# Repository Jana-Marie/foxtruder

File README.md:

# permanently moved to [codeberg/janam/foxtruder](https://codeberg.org/janam/foxtruder)

# foxtruder

**~~froggy~~**, **~~fog-o-nozzle~~**, **~~multimist~~**, **foxtruder [working title]** is a tiny fog machine powered by USB-PD, with Wifi and Bluetooth, based around a 3D-printer heat-cartridge and nozzle. As much as I wish to call this the worlds smallest **intentional** fog machine, sadly disposable vapes exist. Otherwise this one would be atop of the smaller fog-machines. To make it this small however, it requires an external pump, or rather a pressurized fog-fluid line, which can be connected to the 4mm pneumatic connector at the bottom. The idea here is to just have one fog-juice reservoir and pump for many fog machines. A valve on the board is used to switch the fog.

 - **Size:** 70x70x35mm
 - **Power-In:** 12-24V DC, USB-PD
 - **Communication:** RS485, DMX, WIFI, BLE, USB (Python Shell)
 - **Indication:** 4 Status LEDs, 5 Effect LEDs
 - **IO:** RS485, External IO, 2 Buttons, 4mm pneumatic push connector (fluid in), Fan Connector, I2C

Now, you might ask **why**?? To be clear, this is a stupid idea, an intrusive thought turned reality if you will, I'm not even sure if I can recommend you to replicate this. However, the tiny size combined with the low cost per machine of ~20-40€ makes this perfect for larger art-installations requiring fog. Or even better use the fog as the medium of visual art. I.e. in an array, linear arrangement, circular fashion or just many small distributed points of fog generation.

<table>
  <tbody>
    <tr>
      <td>
        
      </td>
      <td>
        
      </td>
    </tr>
  </tbody>
</table>

I guess this exists now, enjoy?.

<table>
  <tbody>
    <tr>
      <td width="68%">
        
      </td>
      <td>
        
      </td>
    </tr>
  </tbody>
</table>

### State of this project and learnings

**It is not recommended to replicate this project in its current form, it is more of an experiment than a proper fog machine.** Issues to be solved include but are not limited to:

 - Spitting, the fog machine tends to not convert all fog-juice into fog
 - BOM cost, it should be optimized
 - Mechanical complexity, the valve-hotend interface requires some odd machining
 - Assembly complexity is too high
 - Open health questions, it seems that fog-juice may be unhealthy when heated above 190°C, however for a proper, spit-free operation temperatures well above 250-300°C might be desired (as with commercial fog machines)

### FAQ

##### Can this be run off a MacBooks USB-PD port?

Yes, that was the main mean of development.

### Initial block diagram

This needs updating, but this was the initial idea. The fog-juice tank is an external component now and the additional airflow controller to disturb the fog has not been implemented yet. Otherwise this is fairly true to foxtruder. The fog-juice tank is a real thing and has an input for pressurized air and an outlet for the liquid.

<table>
  <tbody>
    <tr>
      <td>
        
      </td>
    </tr>
  </tbody>
</table>

### On the name

Finding a name for this project was surprisingly complicated, we just included all names we came up with. The initial idea was to "paint it green and call it froggy", like a foggy small frog sitting in the morning mist of a luscious lawn. Then we went towards focussing on the nozzle, the snoot and eventually we arrived at foxtruder, just... don't boop it, it *will* bite.

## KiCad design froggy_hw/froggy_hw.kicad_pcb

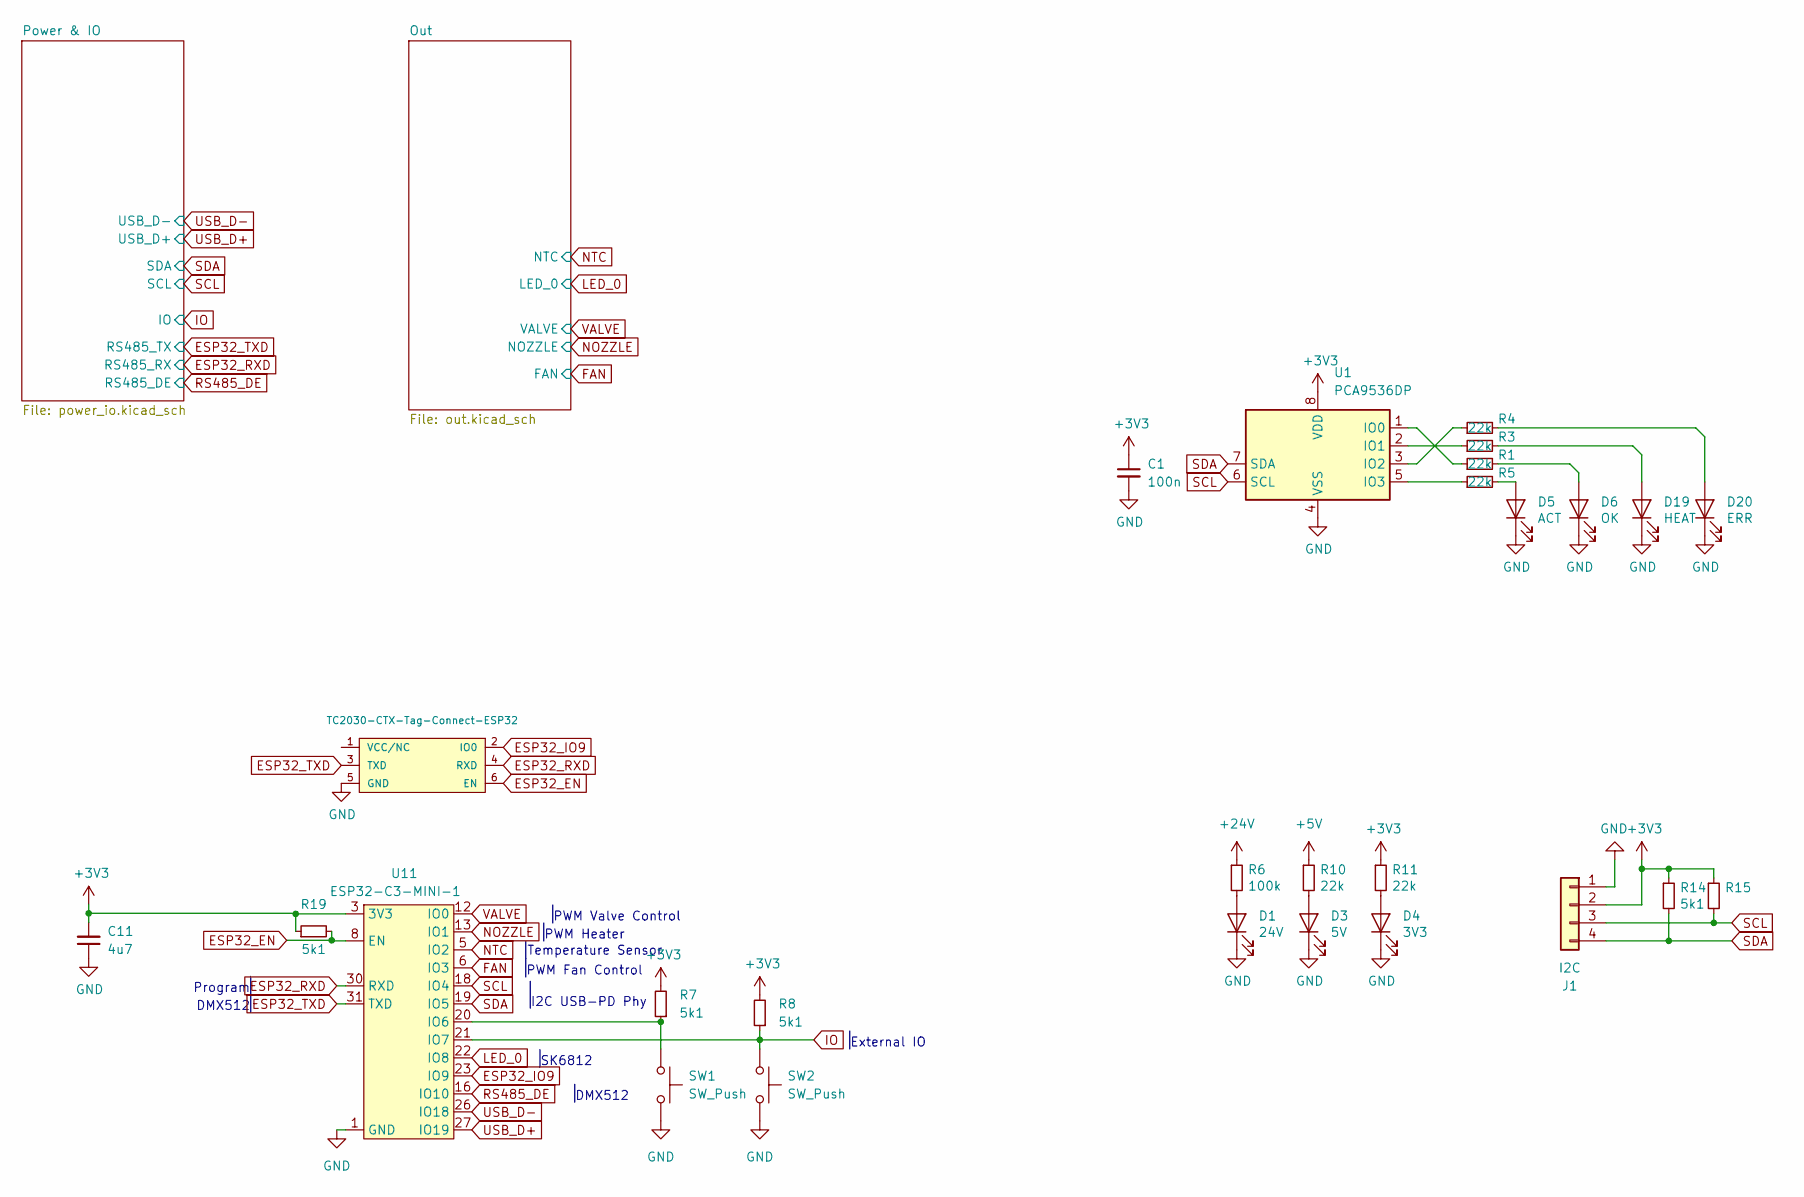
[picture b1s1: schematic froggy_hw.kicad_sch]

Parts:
C1: 100n; C_0402
C11: 4u7; C_0805
D1: 24V; LED_0603_1608Metric
D3: 5V; LED_0603_1608Metric
D4: 3V3; LED_0603_1608Metric
D5: ACT; LED_0603_1608Metric
D6: OK; LED_0603_1608Metric
D19: HEAT; LED_0603_1608Metric
D20: ERR; LED_0603_1608Metric
J1: I2C; PinHeader_1x04_P2.54mm_Vertical_SMD_Pin1Left
P2: TC2030-CTX-Tag-Connect-ESP32; TC2030
R1, R3, R4, R5, R10, R11: 22k; R_0402
R6: 100k; R_0402
R7, R8, R14, R15, R19: 5k1; R_0402
SW1, SW2: SW_Push; SW_SPST_EVQP7C
U1: PCA9536DP; TSSOP-8_3x3mm_P0.65mm
U11: ESP32-C3-MINI-1

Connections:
+3V3: C1.1, C11.2, J1.2, R7.2, R8.2, R11.1, R14.1, R15.1, R19.1, U1.8 (VDD), U11.3 (3V3); also elsewhere on the board
+5V: R10.1; also elsewhere on the board
+24V: R6.1; also elsewhere on the board
ESP32_EN: P2.6 (EN), R19.2, U11.8 (EN)
ESP32_IO9: P2.2 (IO0), U11.23 (IO9)
ESP32_RXD: P2.4 (RXD), U11.30 (RXD); also elsewhere on the board
ESP32_TXD: P2.3 (TXD), U11.31 (TXD); also elsewhere on the board
FAN: U11.6 (IO3)
GND: C1.2, C11.1, D1.1 (K), D3.1 (K), D4.1 (K), D5.1 (K), D6.1 (K), D19.1 (K), D20.1 (K), J1.1, P2.5 (GND), SW1.2, SW2.2, U1.4 (VSS), U11.1 (GND), U11.2 (GND), U11.11 (GND), U11.14 (GND), U11.36 (GND), U11.37 (GND), U11.38 (GND), U11.39 (GND), U11.40 (GND), U11.41 (GND), U11.42 (GND), U11.43 (GND), U11.44 (GND), U11.45 (GND), U11.46 (GND), U11.47 (GND), U11.48 (GND), U11.49 (GND), U11.50 (GND), U11.51 (GND), U11.52 (GND), U11.53 (GND); also elsewhere on the board
IO: R8.1, SW2.1, U11.21 (IO7); also elsewhere on the board
LED_0: U11.22 (IO8); also elsewhere on the board
NOZZLE: U11.13 (IO1); also elsewhere on the board
NTC: U11.5 (IO2); also elsewhere on the board
unnamed: D1.2 (A), R6.2
unnamed: D3.2 (A), R10.2
unnamed: D4.2 (A), R11.2
unnamed: D5.2 (A), R5.2
unnamed: D6.2 (A), R1.2
unnamed: D19.2 (A), R3.2
unnamed: D20.2 (A), R4.2
unnamed: R1.1, U1.1 (IO0)
unnamed: R3.1, U1.2 (IO1)
unnamed: R4.1, U1.3 (IO2)
unnamed: R5.1, U1.5 (IO3)
unnamed: R7.1, SW1.1, U11.20 (IO6)
RS485_DE: U11.16 (IO10); also elsewhere on the board
SCL: J1.3, R15.2, U1.6 (SCL), U11.18 (IO4); also elsewhere on the board
SDA: J1.4, R14.2, U1.7 (SDA), U11.19 (IO5); also elsewhere on the board
USB_D+: U11.27 (IO19); also elsewhere on the board
USB_D-: U11.26 (IO18); also elsewhere on the board
VALVE: U11.12 (IO0); also elsewhere on the board

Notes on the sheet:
External IO
SK6812
PWM Fan Control
PWM Valve Control
DMX512
PWM Heater
Temperature Sensor
Program
I2C USB-PD Phy

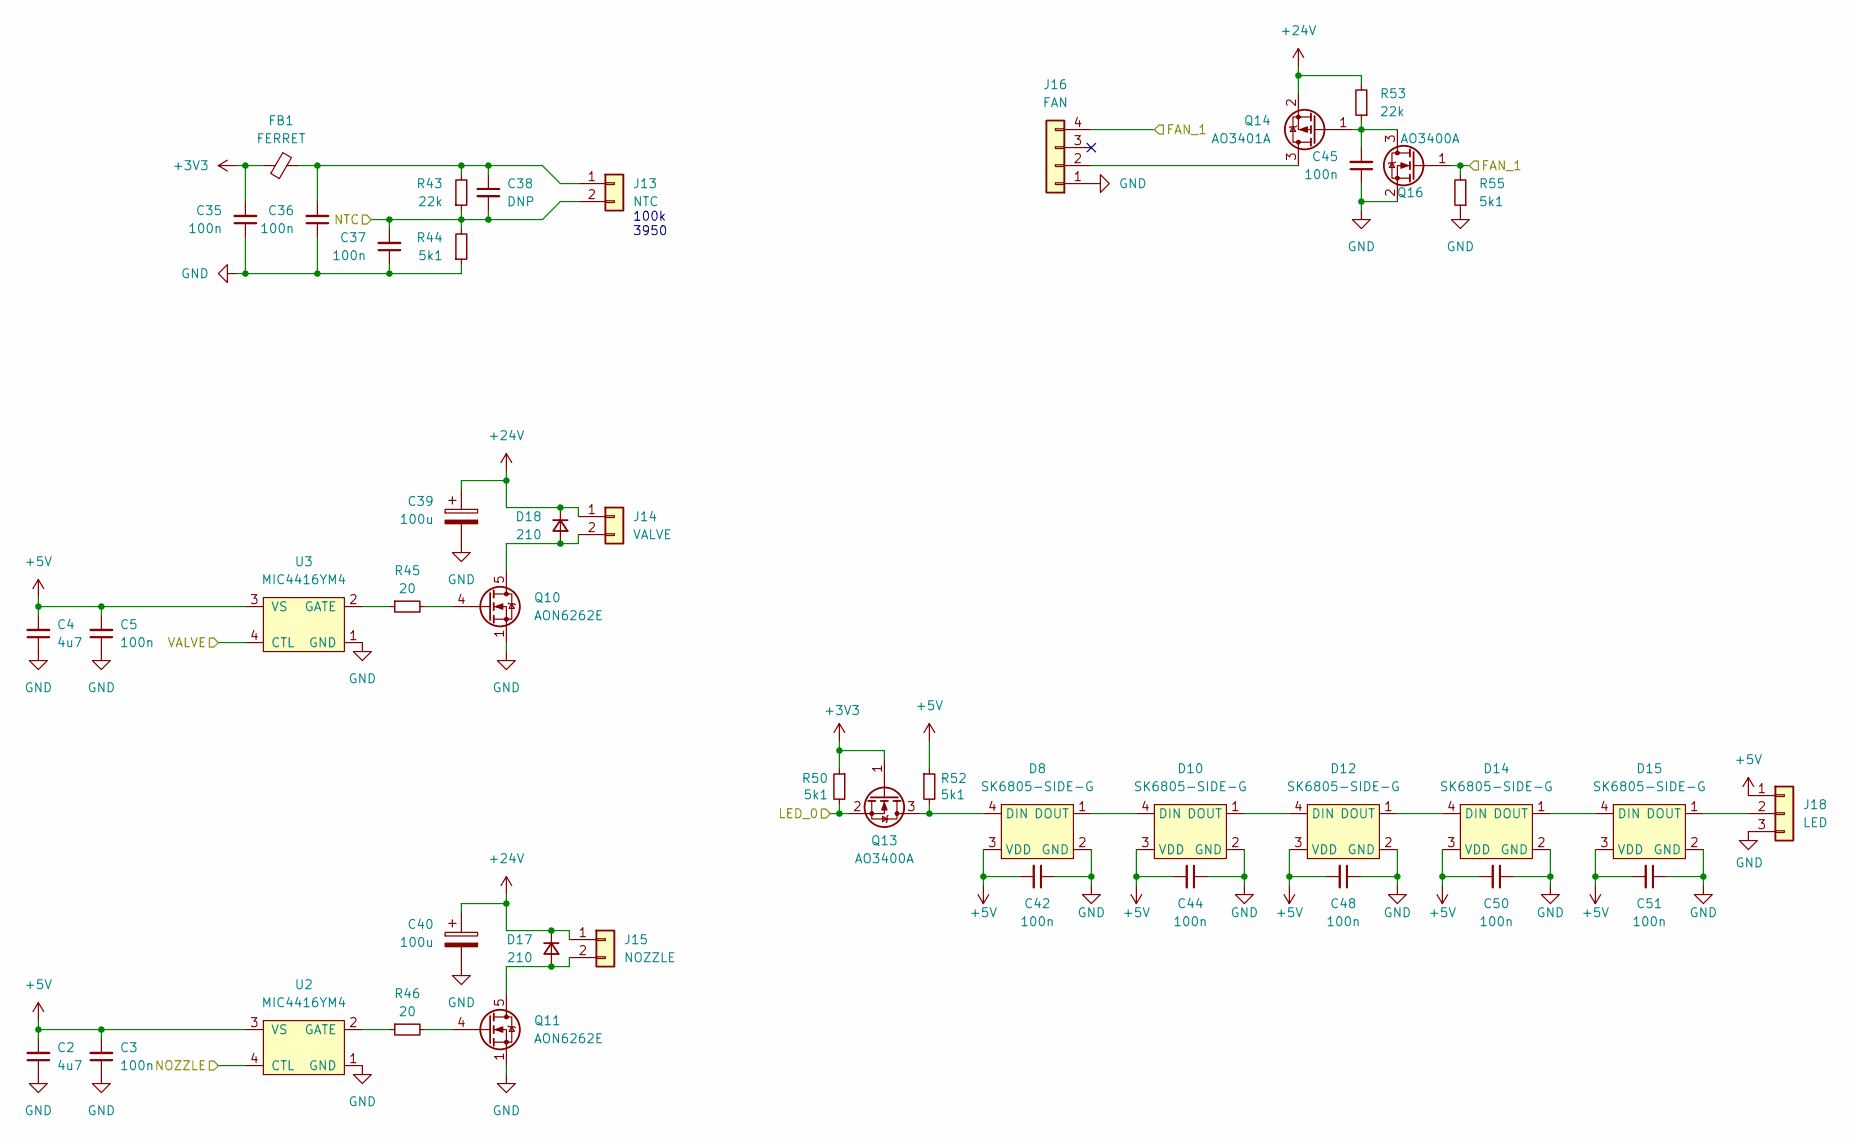
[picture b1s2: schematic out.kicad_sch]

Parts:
C2, C4: 4u7; C_0805
C3, C5, C35, C36, C37, C42, C44, C45, C48, C50, C51: 100n; C_0402
C38: DNP; C_0402
C39, C40: 100u; CP_Radial_D6.3mm_P2.50mm
D8, D10, D12, D14, D15: SK6805-SIDE-G
D17, D18: 210; D_SOD-123F
FB1: FERRET; R_0805
J13: NTC; PinHeader_1x02_P2.54mm_Vertical
J14: VALVE; PhoenixContact_MCV_1,5_2-G-3.5_1x02_P3.50mm_Vertical
J15: NOZZLE; PhoenixContact_MCV_1,5_2-G-3.5_1x02_P3.50mm_Vertical
J16: FAN; Molex_KK-254_AE-6410-04A_1x04_P2.54mm_Vertical
J18: LED; PinHeader_1x03_P2.54mm_Horizontal
Q10, Q11: AON6262E; TDSON-8-1
Q13, Q16: AO3400A; SOT-23
Q14: AO3401A; SOT-23
R43, R53: 22k; R_0402
R44, R50, R52, R55: 5k1; R_0402
R45, R46: 20; R_0805
U2, U3: MIC4416YM4; SOT-143

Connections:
+3V3: C35.2, FB1.1, Q13.1 (G), R50.1; also elsewhere on the board
+5V: C2.2, C3.2, C4.2, C5.2, C42.2, C44.2, C48.2, C50.2, C51.2, D8.3 (VDD), D10.3 (VDD), D12.3 (VDD), D14.3 (VDD), D15.3 (VDD), J18.1, R52.1, U2.3 (VS), U3.3 (VS); also elsewhere on the board
+24V: C39.1, C40.1, D17.1 (K), D18.1 (K), J14.1, J15.1, Q14.2 (S), R53.2; also elsewhere on the board
/Out/FAN_1: J16.4, Q16.1 (G), R55.2
GND: C2.1, C3.1, C4.1, C5.1, C35.1, C36.1, C37.1, C39.2, C40.2, C42.1, C44.1, C45.1, C48.1, C50.1, C51.1, D8.2 (GND), D10.2 (GND), D12.2 (GND), D14.2 (GND), D15.2 (GND), J16.1, J18.3, Q10.1 (S), Q10.2 (S), Q10.3 (S), Q11.1 (S), Q11.2 (S), Q11.3 (S), Q16.2 (S), R44.1, R55.1, U2.1 (GND), U3.1 (GND); also elsewhere on the board
LED_0: Q13.2 (S), R50.2; also elsewhere on the board
NOZZLE: U2.4 (CTL); also elsewhere on the board
NTC: C37.2, C38.2, J13.2, R43.1, R44.2; also elsewhere on the board
unnamed: D8.4 (DIN), Q13.3 (D), R52.2
unnamed: D8.1 (DOUT), D10.4 (DIN)
unnamed: D10.1 (DOUT), D12.4 (DIN)
unnamed: D12.1 (DOUT), D14.4 (DIN)
unnamed: D14.1 (DOUT), D15.4 (DIN)
unnamed: D15.1 (DOUT), J18.2
unnamed: D17.2 (A), J15.2, Q11.5 (D)
unnamed: D18.2 (A), J14.2, Q10.5 (D)
unnamed: C36.2, C38.1, FB1.2, J13.1, R43.2
unnamed: J16.2, Q14.3 (D)
unnamed: Q10.4 (G), R45.2
unnamed: Q11.4 (G), R46.2
unnamed: C45.2, Q14.1 (G), Q16.3 (D), R53.1
unnamed: R46.1, U2.2 (GATE)
unnamed: R45.1, U3.2 (GATE)
VALVE: U3.4 (CTL); also elsewhere on the board

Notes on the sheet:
100k 3950

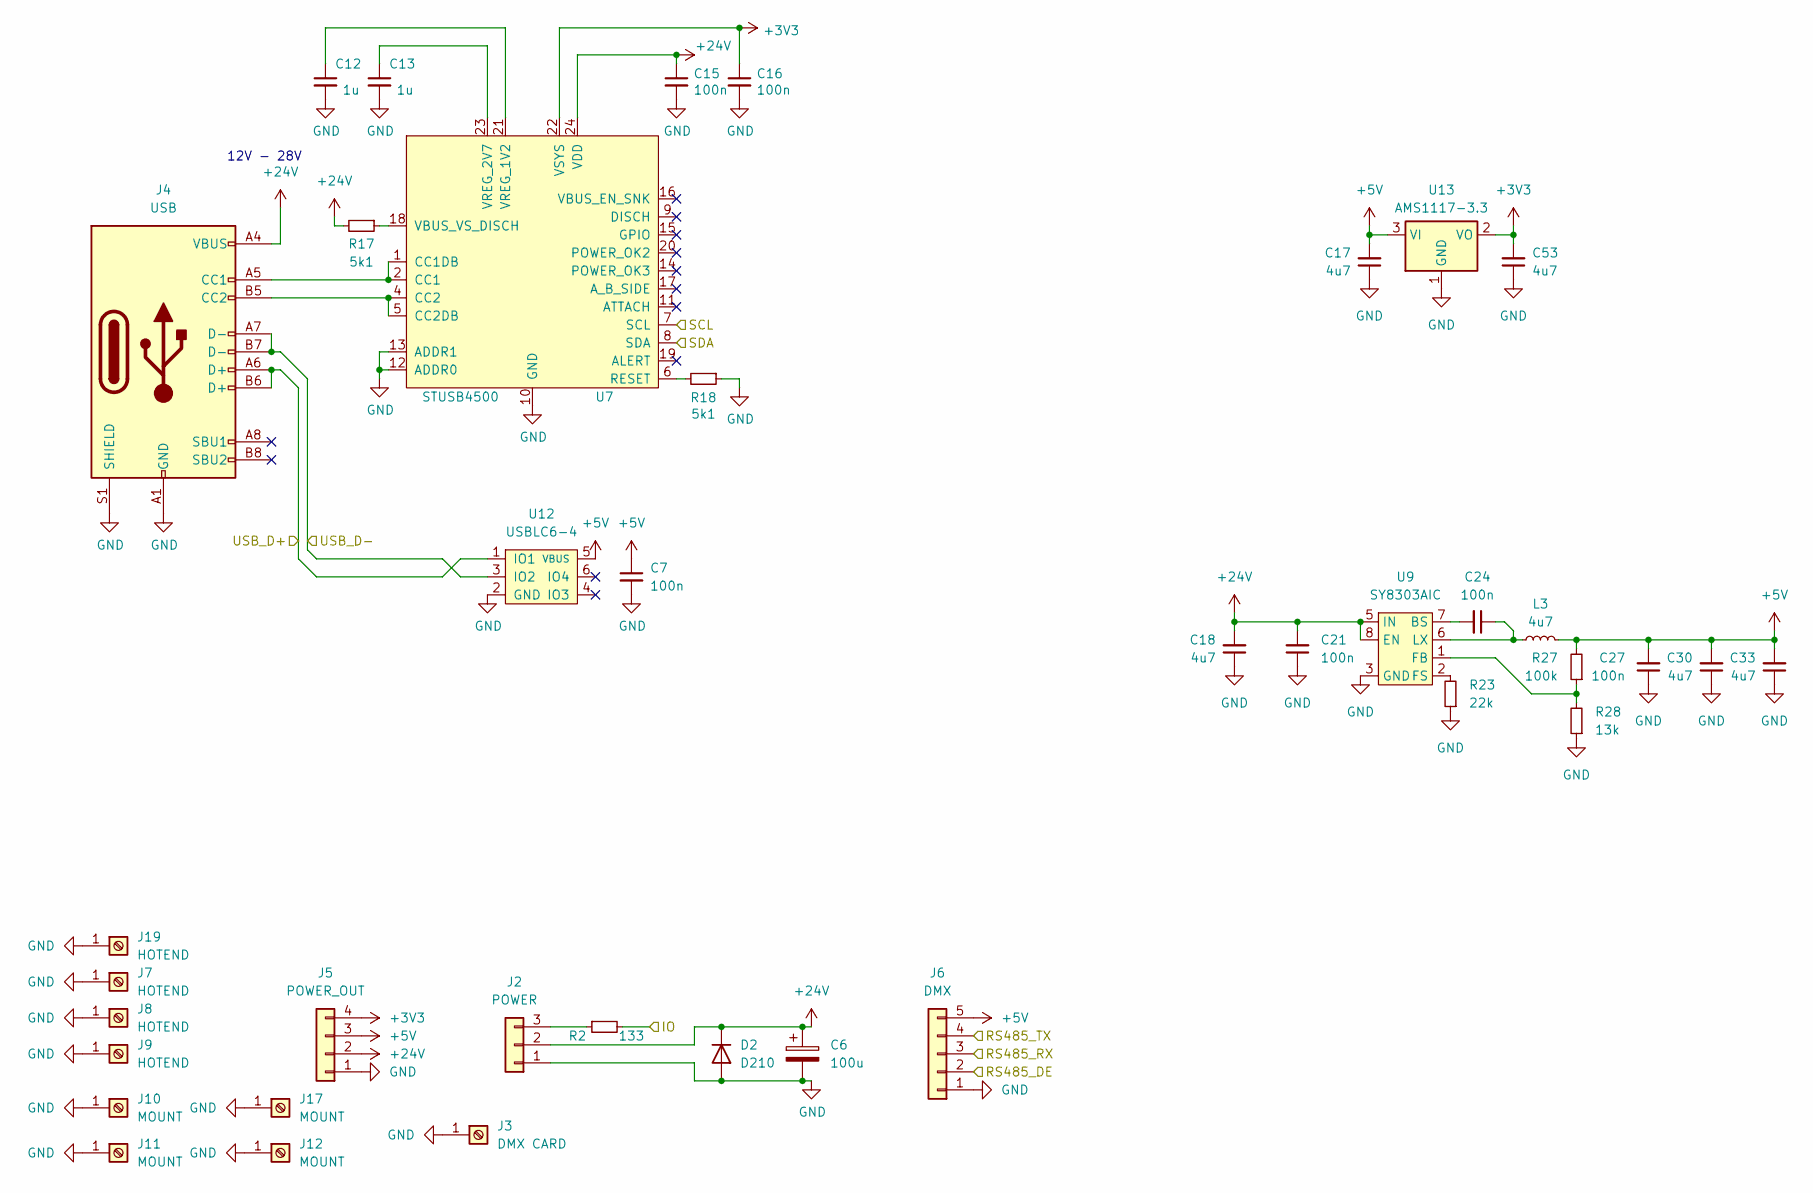
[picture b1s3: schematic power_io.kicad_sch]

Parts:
C6: 100u; CP_Radial_D6.3mm_P2.50mm
C7, C15, C16, C21, C27: 100n; C_0402
C12, C13: 1u; C_0603
C17, C18, C30, C33, C53: 4u7; C_0805
C24: 100n; C_0603
D2: D210; D_SMA
J2: POWER; PhoenixContact_MC_1,5_3-G-3.5_1x03_P3.50mm_Horizontal
J3: DMX CARD; MountingHole_2.2mm_M2_Pad_Via
J4: USB; USB-C 16Pin
J5: POWER_OUT; PinHeader_1x04_P2.54mm_Horizontal
J6: DMX; PinHeader_1x05_P2.54mm_Horizontal
J7, J8, J9, J19: HOTEND; froggy_PAD
J10, J11, J12, J17: MOUNT; MountingHole_2.2mm_M2_Pad_Via
L3: 4u7; L_Taiyo-Yuden_MD-4040
R2: 133; R_0805
R17, R18: 5k1; R_0402
R23: 22k; R_0402
R27: 100k; R_0402
R28: 13k; R_0402
U7: STUSB4500; QFN-24-1EP_4x4mm_P0.5mm_EP2.7x2.7mm
U9: SY8303AIC; TSOT-23-8
U12: USBLC6-4; SOT-23-6
U13: AMS1117-3.3; SOT-223-3_TabPin2

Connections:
+3V3: C16.1, C53.2, J5.4, U7.22 (VSYS), U13.2 (VO); also elsewhere on the board
+5V: C7.1, C17.2, C27.2, C30.2, C33.2, J5.3, J6.5, L3.2, R27.2, U12.5 (VBUS), U13.3 (VI); also elsewhere on the board
+24V: C6.1, C15.1, C18.2, C21.2, D2.1 (K), J2.2, J4.A4 (VBUS), J4.A9 (VBUS), J4.B4 (VBUS), J4.B9 (VBUS), J5.2, R17.2, U7.24 (VDD), U9.5 (IN), U9.8 (EN); also elsewhere on the board
ESP32_RXD: J6.3; also elsewhere on the board
ESP32_TXD: J6.4; also elsewhere on the board
GND: C6.2, C7.2, C12.2, C13.2, C15.2, C16.2, C17.1, C18.1, C21.1, C27.1, C30.1, C33.1, C53.1, D2.2 (A), J2.1, J3.1, J4.A1 (GND), J4.A12 (GND), J4.B1 (GND), J4.B12 (GND), J4.S1 (SHIELD), J5.1, J6.1, J7.1, J8.1, J9.1, J10.1, J11.1, J12.1, J17.1, J19.1, R18.1, R23.1, R28.1, U7.10 (GND), U7.12 (ADDR0), U7.13 (ADDR1), U7.25 (GND), U9.3 (GND), U9.4 (GND), U12.2 (GND), U13.1 (GND); also elsewhere on the board
IO: R2.2; also elsewhere on the board
unnamed: J2.3, R2.1
unnamed: J4.A5 (CC1), U7.1 (CC1DB), U7.2 (CC1)
unnamed: J4.B5 (CC2), U7.4 (CC2), U7.5 (CC2DB)
unnamed: R18.2, U7.6 (RESET)
unnamed: R17.1, U7.18 (VBUS_VS_DISCH)
unnamed: C12.1, U7.21 (VREG_1V2)
unnamed: C13.1, U7.23 (VREG_2V7)
unnamed: C24.2, U9.7 (BS)
unnamed: R27.1, R28.2, U9.1 (FB)
unnamed: R23.2, U9.2 (FS)
unnamed: C24.1, L3.1, U9.6 (LX)
RS485_DE: J6.2; also elsewhere on the board
SCL: U7.7 (SCL); also elsewhere on the board
SDA: U7.8 (SDA); also elsewhere on the board
USB_D+: J4.A6 (D+), J4.B6 (D+), U12.1 (IO1); also elsewhere on the board
USB_D-: J4.A7 (D-), J4.B7 (D-), U12.3 (IO2); also elsewhere on the board

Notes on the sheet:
12V - 28V

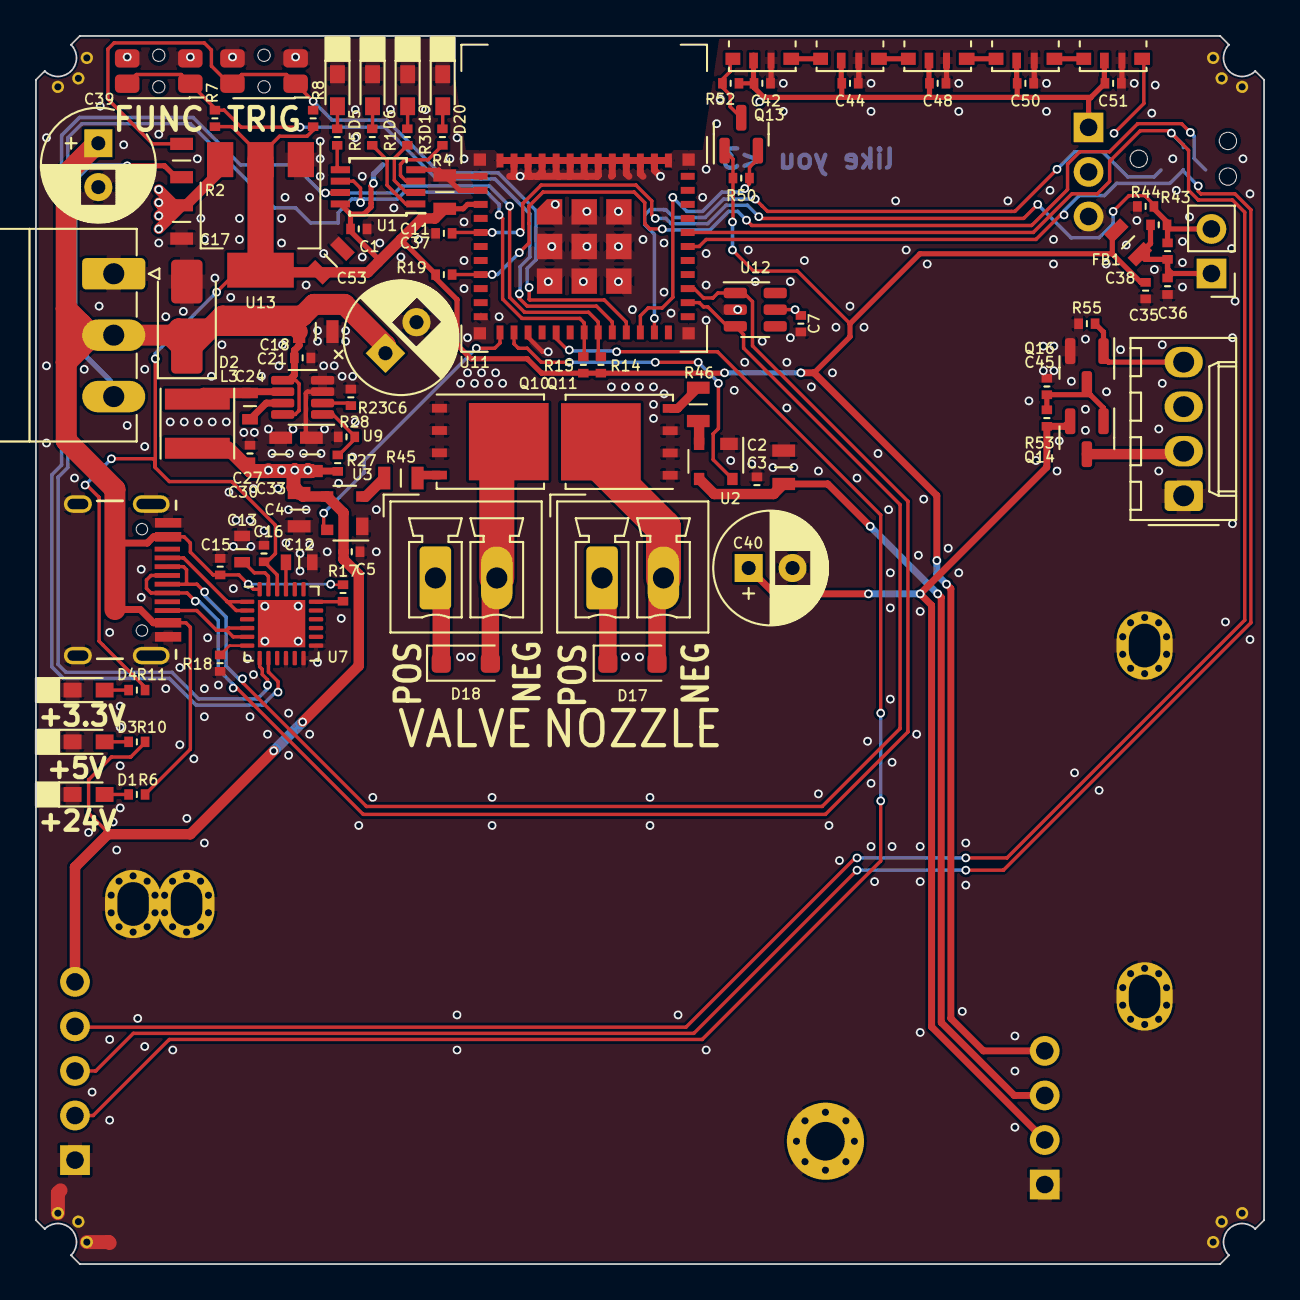
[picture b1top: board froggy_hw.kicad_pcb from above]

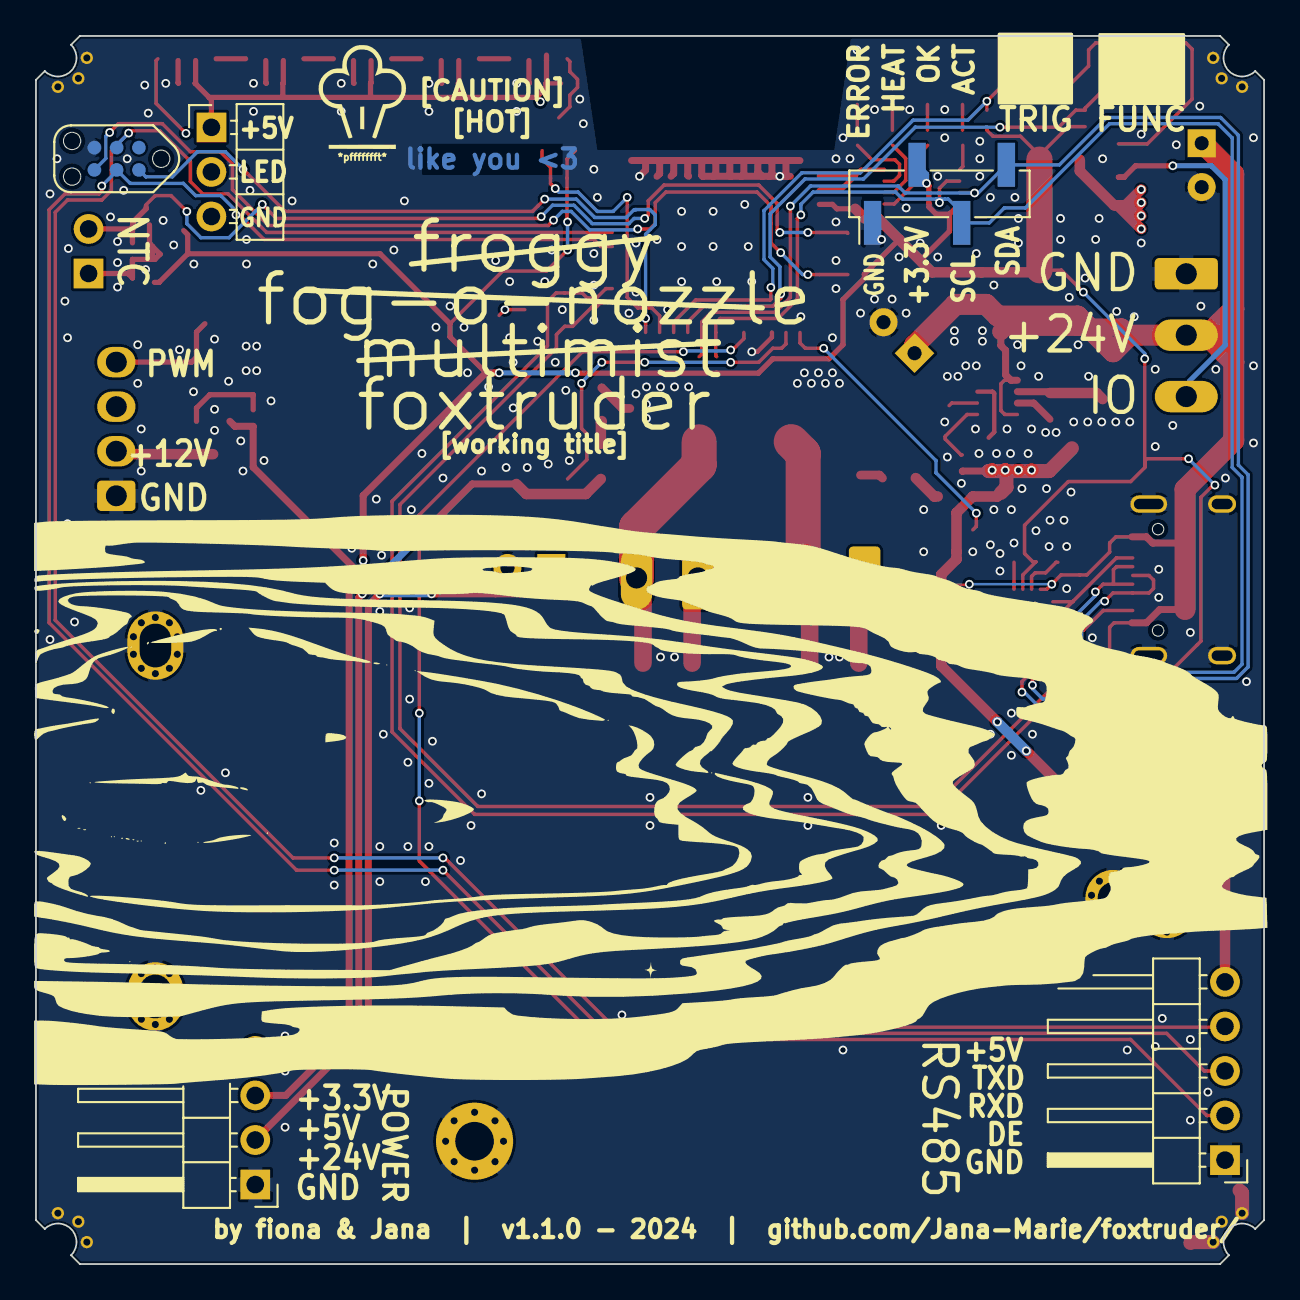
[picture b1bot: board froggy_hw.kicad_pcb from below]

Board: 4 copper layers, 70.0 x 70.0 mm, 110 parts (5 on the bottom side), 57 nets.

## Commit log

2024-03-10 added gitignore
2024-03-10 added hw
2024-03-10 added fw
2024-05-29 moved to esp32
2024-05-29 added supplementaaary file
2025-06-06 updated to new kicad version
2025-06-06 added conceptual drawing
2025-06-06 added decoartions
2025-06-06 removed old firmware
2025-06-06 added firmware v1 to gitignore
2025-06-06 added image
2025-06-06 Add new MicroPython Based Firmware
2025-06-06 added learning
2025-06-06 added two more images
2025-06-06 added table styling
2026-05-14 added emphasis
